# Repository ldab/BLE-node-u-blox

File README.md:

# BLE-node-u-blox

u-blox NINA-B3 BLE node, based on nRF52840 and SHTC3

## TODO

- [ ] 3D enclosure

## Energy Budget

* ?? mA active current;
* Wakes every hour;
* 17uA Sleep current;
* CR2032 ~235mAh;

**Battery life =**

## Nordic SDK

* This is based on nRF5_SDK_16.0.0_98a08e2, get yours here: https://www.nordicsemi.com/Software-and-tools/Software/nRF5-SDK/Download

## Cloud Gateway

* Raspberry Pi + Grafana + InfluxDB;

https://github.com/ldab/BLE-Weather-Station-Cloud-Gateway

## Running the code locally

1. Clone this repo to a local folder ```> git clone https://github.com/ldab/BLE-node-u-blox```
2. Point the `$(SDK)` @`./code/ninab3/blank/ses/libuarte_pca10056.emProject` to where you have installed Nordic SDK, for example `C:\nRF\nRF5_SDK_16.0.0_98a08e2`
3. Like so: `macros="CMSIS_CONFIG_TOOL=C:/nRF/nRF5_SDK_16.0.0_98a08e2/external_tools/cmsisconfig/CMSIS_Configuration_Wizard.jar;SDK=C:/nRF/nRF5_SDK_16.0.0_98a08e2"`
4. Open the SEGGER Embedded Studio project file located in `./code/ninab3/blank/ses/libuarte_pca10056.emProject`

Ref. https://devzone.nordicsemi.com/f/nordic-q-a/44638/how-to-move-an-sdk-example-out-of-the-sdk-tree

## Code reminders

* BSP LEDs status https://infocenter.nordicsemi.com/index.jsp?topic=%2Fsdk_nrf5_v16.0.0%2Fexamples_bsp.html&anchor=examples_bsp_states

## SHTC3 Low Power mode tradeoff

## PCB

## Schematic

## BOM

[Bill of materials](./PCB/BLE-node.csv)

## Enclosure

## Kown issues, limintations

* .

## Final Thoughts or Improvements

* Better battery measurement to avoid current drain;

## Credits

* GitHub Shields and Badges created with [Shields.io](https://github.com/badges/shields/);

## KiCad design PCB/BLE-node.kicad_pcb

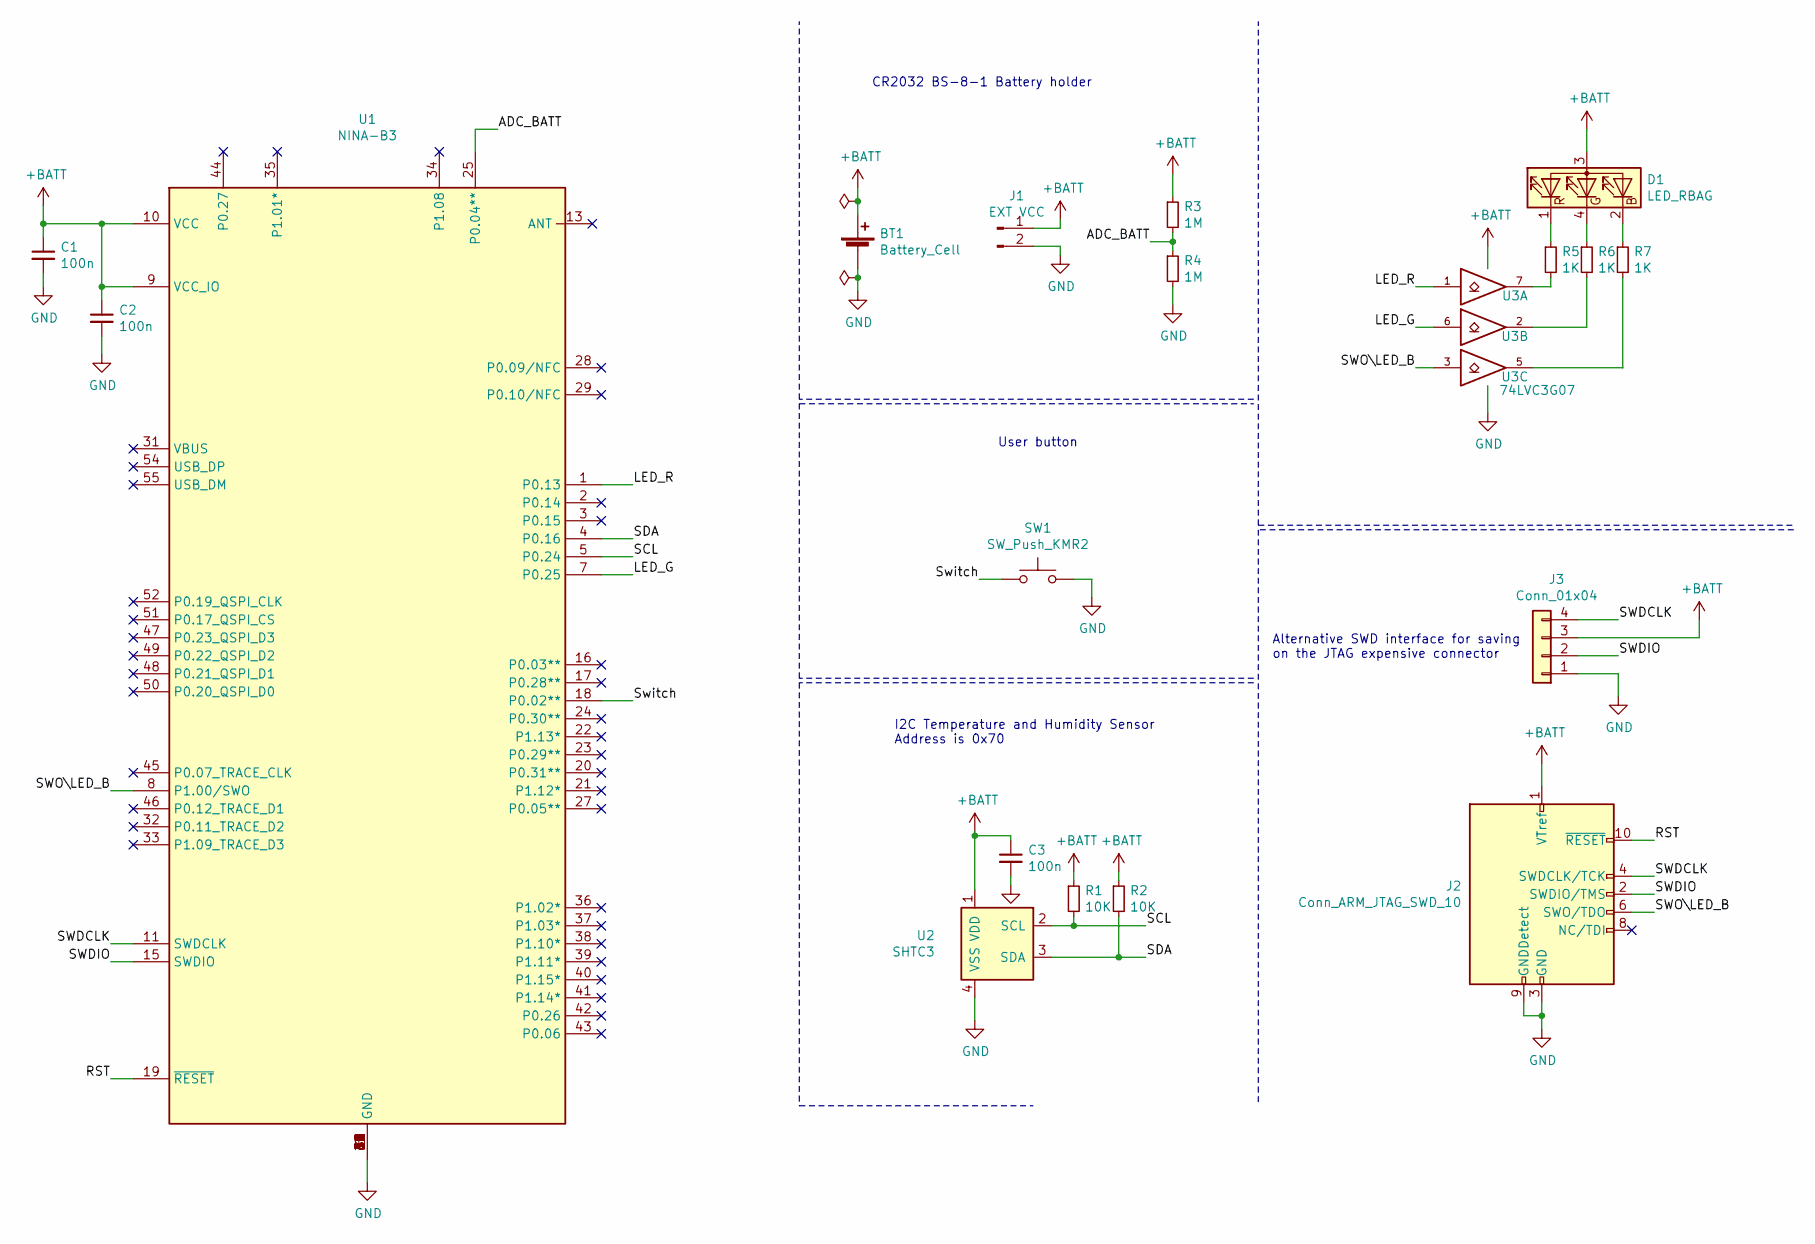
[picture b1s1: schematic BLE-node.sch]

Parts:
BT1: Battery_Cell; BS-8-1; LCSC C70378
C1, C2, C3: 100n; C_0603_1608Metric; LCSC C338036
D1: LED_RBAG; LED_Cree-PLCC4_2x2mm_CW; LCSC C108793
J1: EXT VCC; PinHeader_1x02_P2.00mm_Vertical; LCSC C376075
J2: Conn_ARM_JTAG_SWD_10; SWD_JTAG; LCSC C180221
J3: Conn_01x04; PinHeader_2x02_P2.00mm_Vertical
R1, R2: 10K; R_0603_1608Metric; LCSC C25999
R3, R4: 1M; R_0603_1608Metric; LCSC C384461
R5, R6, R7: 1K; R_0603_1608Metric; LCSC C25585
SW1: SW_Push_KMR2; SW_Push_1P1T_NO_CK_KMR2; LCSC C128941
U1: NINA-B3
U2: SHTC3; AMS_QFN-4-1EP_2x2mm_P0.95mm_EP0.7x1.6mm; LCSC C194656
U3: 74LVC3G07; TSSOP-8_3x3mm_P0.65mm; LCSC C282358

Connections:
+BATT: BT1.1 (+), C1.1, C2.1, C3.1, D1.3 (A), J1.1, J2.1 (VTref), J3.3, R1.1, R2.1, R3.1, U1.9 (VCC_IO), U1.10 (VCC), U2.1 (VDD), U3.8 (VCC)
/ADC_BATT: R3.2, R4.1, U1.25 (P0.04**)
/LED_G: U1.7 (P0.25), U3.6
/LED_R: U1.1 (P0.13), U3.1
/RST: J2.10 (~RESET~), U1.19 (~RESET)
/SCL: R1.2, U1.5 (P0.24), U2.2 (SCL)
/SDA: R2.2, U1.4 (P0.16), U2.3 (SDA)
/SWDCLK: J2.4 (SWDCLK/TCK), J3.4, U1.11 (SWDCLK)
/SWDIO: J2.2 (SWDIO/TMS), J3.2, U1.15 (SWDIO)
/SWO\LED_B: J2.6 (SWO/TDO), U1.8 (P1.00/SWO), U3.3
/Switch: SW1.1, U1.18 (P0.02**)
GND: BT1.2 (-), C1.2, C2.2, C3.2, J1.2, J2.3 (GND), J2.5 (GND), J2.9 (GNDDetect), J3.1, R4.2, SW1.2, U1.6 (GND), U1.12 (GND), U1.14 (GND), U1.26 (GND), U1.30 (GND), U1.53 (GND), U1.56 (GND), U1.57 (GND), U1.58 (GND), U1.59 (GND), U1.60 (GND), U1.61 (GND), U1.62 (GND), U1.63 (GND), U1.64 (GND), U1.65 (GND), U1.66 (GND), U1.67 (GND), U1.68 (GND), U1.69 (GND), U1.70 (GND), U1.71 (GND), U2.4 (VSS), U3.4 (GND)
unnamed: D1.1 (RK), R5.1
unnamed: D1.2 (BK), R7.1
unnamed: D1.4 (GK), R6.1
unnamed: R5.2, U3.7
unnamed: R6.2, U3.2
unnamed: R7.2, U3.5

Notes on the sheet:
I2C Temperature and Humidity Sensor Address is 0x70
Alternative SWD interface for saving on the JTAG expensive connector
User button
CR2032 BS-8-1 Battery holder

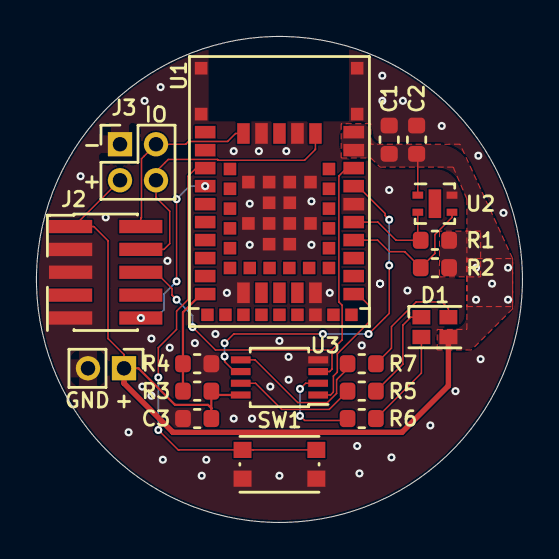
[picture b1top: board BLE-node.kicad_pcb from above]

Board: 2 copper layers, 27.0 x 27.0 mm, 19 parts (1 on the bottom side), 18 nets.

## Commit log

2020-01-23 untested I2C lib
2020-01-29 gerber files
2020-04-09 update dependancies, I2C lib, button and LEDs
2020-04-09 ADC by registers
2020-04-11 ble advertising info
2020-04-13 non-connectable advertising
2020-04-13 timer to start advertising again
2020-04-14 17us sleep and 50us adv@1sec
2020-11-24 nice graph
2023-07-30 dry run
2023-07-31 shtc3

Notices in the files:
README.md:
License: MIT
